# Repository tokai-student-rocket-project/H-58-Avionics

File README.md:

# H-58 搭載計器

TSRP-H-58に搭載する計器類のプログラム及び設計書を保存するレポジトリです。

## はじめに

学生ロケットの電装系を盛り上げたい思いから、全てのソースコードを含む設計を公開しています。ガバガバ開発ですので、分かりにくい点（資料がまとまっていないなど）が多々あります。ご了承ください。

ご不明な点は以下のSNSからお気軽にお問合せください。

- X (旧Twitter): [@Tokai_SRP](https://twitter.com/Tokai_SRP)

### 計器の概要

H-58搭載計器はCANBUS接続された複数のモジュールから構成されます。

### レポジトリ構成

#### ./Components/Modules/

- [SystemDataCommunicationModule](./Components/Modules/SystemDataCommunicationModule/README.md)  
- [AirDataCommunicationModule](./Components/Modules/AirDataCommunicationModule/README.md) 
- [FlightModule](./Components/Modules/FlightModule/README.md)  
- [SensingModule](./Components/Modules/SensingModule/README.md) 
- [ValveControlModule](./Components/Modules/ValveContolModule/README.md) 
- [MissionModule](./Components/Modules/MissionModule/README.md) 
- [PowerModule](./Components/Modules/PowerModule/README.md) 

#### ./Documents/

- 開発資料
  - [工程計画書](./Documents/Materials/Schedule.md)
  - [要件定義書](./Documents/Materials/RequirementsDocument.md)
  - [基本設計書](./Documents/Materials/BasicDesignDocument.md)
  - [詳細設計書](./Documents/Materials/DetailedDesignDocument.md)
- 安全審査
  - [一次審査(Z-storage)](https://docs.google.com/document/d/1F-2k9H3952sz7PHYDDPXtUgwHEACfZ0U/edit?usp=sharing&ouid=102715455383884127068&rtpof=true&sd=true)
  - [二次審査(Z-storage)](https://drive.google.com/file/d/1VNDg2A9r9_NxHciDonn3Oh5dWTKx7AV1/view?usp=sharing)
- マニュアル
  - [部品一覧](./Documents/Materials/Manual/PartsList.md)
  - 手順書
    - [組み立て手順書](./Documents/Materials/Manual/Procedure/AssemblyProcedure.md)
- [詳細報告書](./Documents/Reports/DetailedRaport.pdf) (一番情報量多い)

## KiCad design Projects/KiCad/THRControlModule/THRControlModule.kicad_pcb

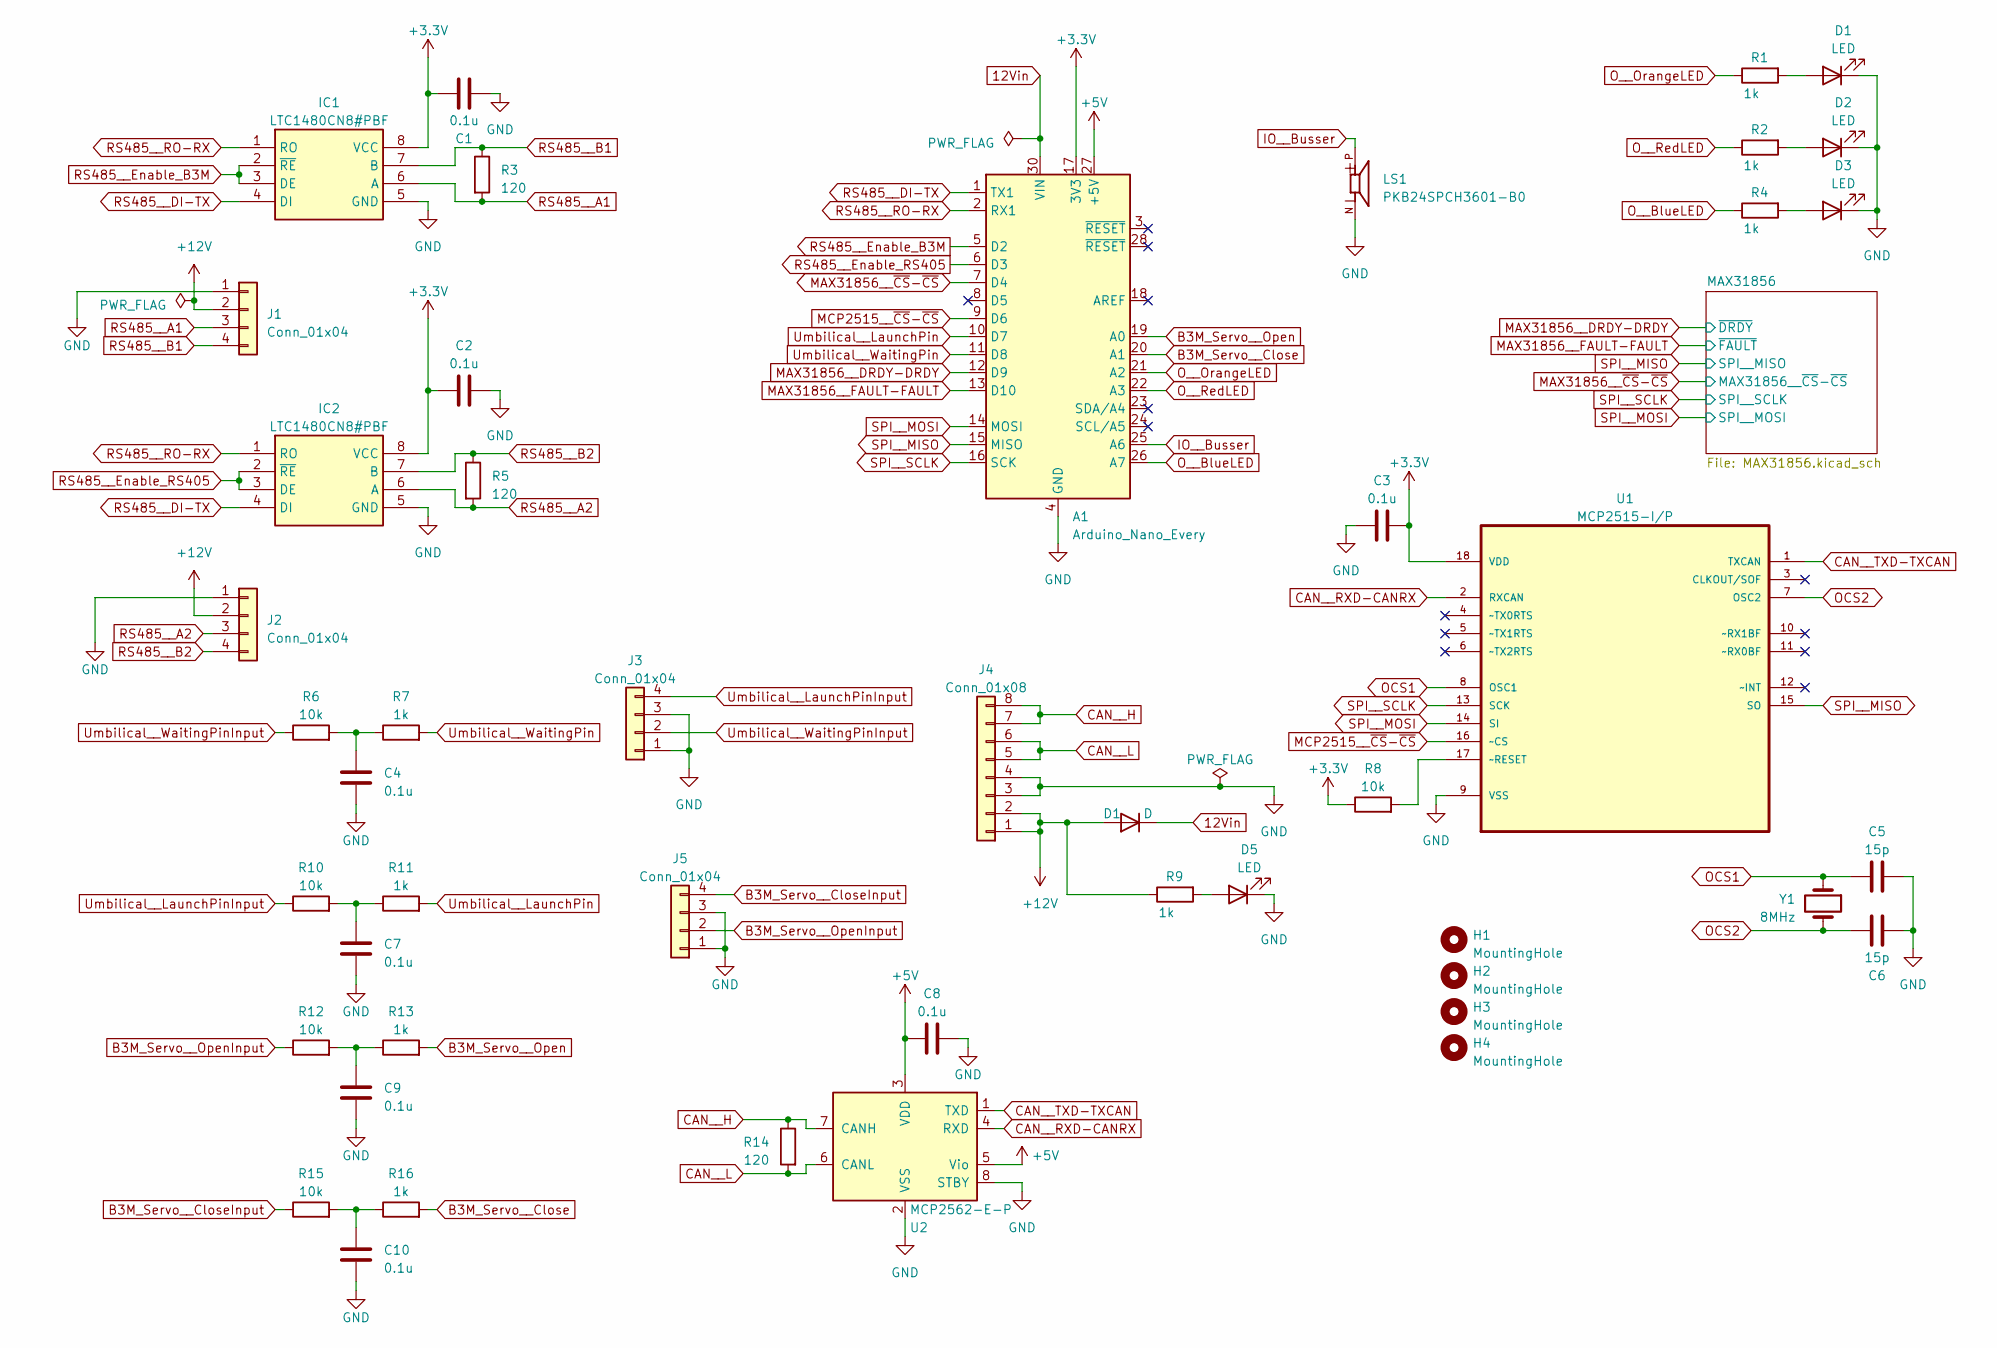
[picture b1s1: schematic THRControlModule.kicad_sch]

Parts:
A1: Arduino_Nano_Every; Arduino_Nano
C1, C2, C3, C4, C7, C8, C9, C10: 0.1u; C_0603_1608Metric_Pad1.08x0.95mm_HandSolder
C5, C6: 15p; C_0603_1608Metric_Pad1.08x0.95mm_HandSolder
D1: D; D_SOD-123
D2, D3, D5: LED; LED_0603_1608Metric_Pad1.05x0.95mm_HandSolder
H1, H2, H3, H4: MountingHole; MountingHole_4.5mm
IC1, IC2: LTC1480CN8#PBF; DIP794W53P254L1016H394Q8N; Manufacturer_Part_Number LTC1480CN8#PBF; Mouser Part Number 584-LTC1480CN8#PBF
J1, J2, J3, J5: Conn_01x04; Hirose_DF1BZ-4P-2.5DS
J4: Conn_01x08; Hirose_DF11B-8DP-2DS
LS1: PKB24SPCH3601-B0; SPKR_PKB24SPCH3601-B0; PARTREV March 24, 2017
R1, R2, R4, R7, R9, R11, R13, R16: 1k; R_0603_1608Metric_Pad0.98x0.95mm_HandSolder
R3, R5, R14: 120; R_0603_1608Metric_Pad0.98x0.95mm_HandSolder
R6, R8, R10, R12, R15: 10k; R_0603_1608Metric_Pad0.98x0.95mm_HandSolder
U1: MCP2515-I/P; DIP254P762X432-18; MPN MCP2515-I/P
U2: MCP2562-E-P; DIP-8_W7.62mm
Y1: 8MHz; Crystal_HC49-4H_Vertical

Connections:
+3.3V: A1.17 (3V3), C1.1, C2.1, C3.2, IC1.8 (VCC), IC2.8 (VCC), R8.1, U1.18 (VDD); also elsewhere on the board
+5V: A1.27 (+5V), C8.1, U2.3 (VDD), U2.5 (Vio)
B3M_Servo__Close: A1.20 (A1), R16.2
B3M_Servo__CloseInput: J5.4, R15.1
B3M_Servo__Open: A1.19 (A0), R13.2
B3M_Servo__OpenInput: J5.2, R12.1
CAN__H: J4.7, J4.8, R14.1, U2.7 (CANH)
CAN__L: J4.5, J4.6, R14.2, U2.6 (CANL)
CAN__RXD-CANRX: U1.2 (RXCAN), U2.4 (RXD)
CAN__TXD-TXCAN: U1.1 (TXCAN), U2.1 (TXD)
IO__Busser: A1.25 (A6), LS1.P
MAX31856__DRDY-DRDY: A1.12 (D9); also elsewhere on the board
MAX31856__FAULT-FAULT: A1.13 (D10); also elsewhere on the board
MAX31856__~CS-~CS: A1.7 (D4); also elsewhere on the board
MCP2515__~CS-~CS: A1.9 (D6), U1.16 (~CS)
unnamed: C4.1, R6.2, R7.1
unnamed: C7.1, R10.2, R11.1
unnamed: C9.1, R12.2, R13.1
unnamed: C10.1, R15.2, R16.1
unnamed: D2.2 (A), R2.2
unnamed: D3.2 (A), R4.2
unnamed: D5.2 (A), R9.2
unnamed: R8.2, U1.17 (~RESET)
OCS1: C5.1, U1.8 (OSC1), Y1.1
OCS2: C6.1, U1.7 (OSC2), Y1.2
O__BlueLED: A1.26 (A7), R4.1
O__OrangeLED: A1.21 (A2), R1.1
O__RedLED: A1.22 (A3), R2.1
RS485__A1: IC1.6 (A), J1.3, R3.2
RS485__A2: IC2.6 (A), J2.3, R5.2
RS485__B1: IC1.7 (B), J1.4, R3.1
RS485__B2: IC2.7 (B), J2.4, R5.1
RS485__DI-TX: A1.1 (TX1), IC1.4 (DI), IC2.4 (DI)
RS485__Enable_B3M: A1.5 (D2), IC1.2 (~RE), IC1.3 (DE)
RS485__Enable_RS405: A1.6 (D3), IC2.2 (~RE), IC2.3 (DE)
RS485__RO-RX: A1.2 (RX1), IC1.1 (RO), IC2.1 (RO)
SPI__MISO: A1.15 (MISO), U1.15 (SO); also elsewhere on the board
SPI__MOSI: A1.14 (MOSI), U1.14 (SI); also elsewhere on the board
SPI__SCLK: A1.16 (SCK), U1.13 (SCK); also elsewhere on the board
Umbilical__LaunchPin: A1.10 (D7), R11.2
Umbilical__LaunchPinInput: J3.4, R10.1
Umbilical__WaitingPin: A1.11 (D8), R7.2
Umbilical__WaitingPinInput: J3.2, R6.1

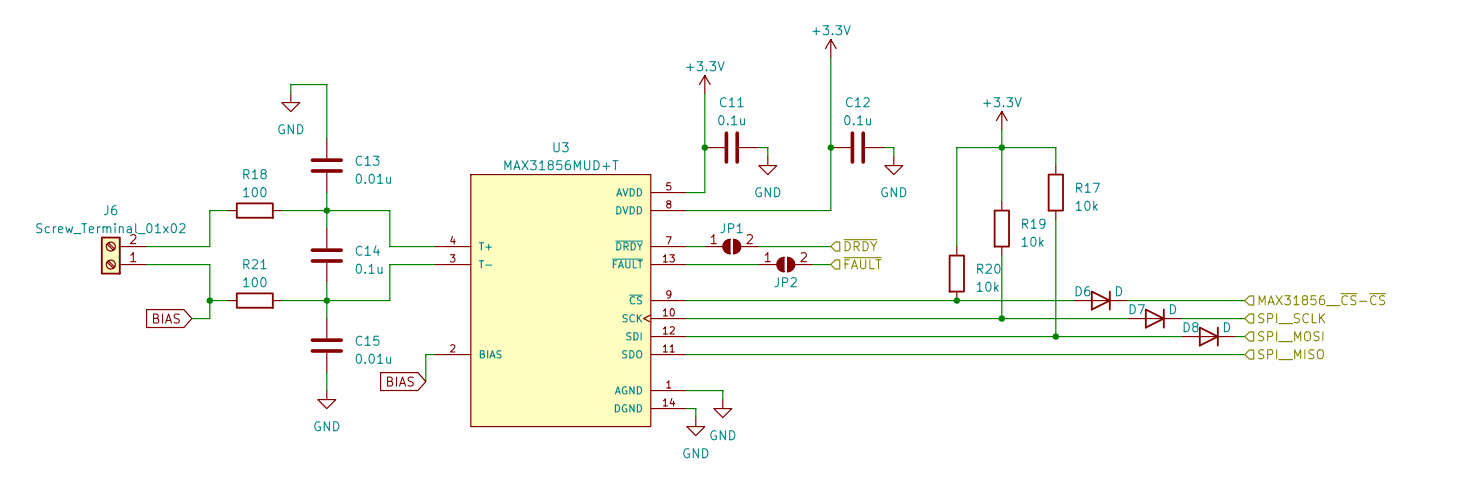
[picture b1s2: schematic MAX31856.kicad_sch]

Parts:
C11, C12, C14: 0.1u; C_0603_1608Metric_Pad1.08x0.95mm_HandSolder
C13, C15: 0.01u; C_0603_1608Metric_Pad1.08x0.95mm_HandSolder
D6, D7, D8: D; D_SOD-123
J6: Screw_Terminal_01x02; RS_PRO_611-8157
JP1, JP2: SolderJumper_2_Open; SolderJumper-2_P1.3mm_Open_Pad1.0x1.5mm
R17, R19, R20: 10k; R_0603_1608Metric_Pad0.98x0.95mm_HandSolder
R18, R21: 100; R_0805_2012Metric_Pad1.20x1.40mm_HandSolder
U3: MAX31856MUD+T; SOP65P640X110-14N; PARTREV 0

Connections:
+3.3V: C11.1, C12.1, R17.1, R19.1, R20.1, U3.5 (AVDD), U3.8 (DVDD); also elsewhere on the board
BIAS: J6.1, R21.1, U3.2 (BIAS)
MAX31856__DRDY-DRDY: JP1.2 (B); also elsewhere on the board
MAX31856__FAULT-FAULT: JP2.2 (B); also elsewhere on the board
MAX31856__~CS-~CS: D6.1 (K); also elsewhere on the board
unnamed: D6.2 (A), R20.2, U3.9 (~CS)
unnamed: D7.2 (A), R19.2, U3.10 (SCK)
unnamed: D8.2 (A), R17.2, U3.12 (SDI)
unnamed: J6.2, R18.1
unnamed: JP1.1 (A), U3.7 (~DRDY)
unnamed: JP2.1 (A), U3.13 (~FAULT)
unnamed: C13.2, C14.1, R18.2, U3.4 (T+)
unnamed: C14.2, C15.1, R21.2, U3.3 (T-)
SPI__MISO: U3.11 (SDO); also elsewhere on the board
SPI__MOSI: D8.1 (K); also elsewhere on the board
SPI__SCLK: D7.1 (K); also elsewhere on the board

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
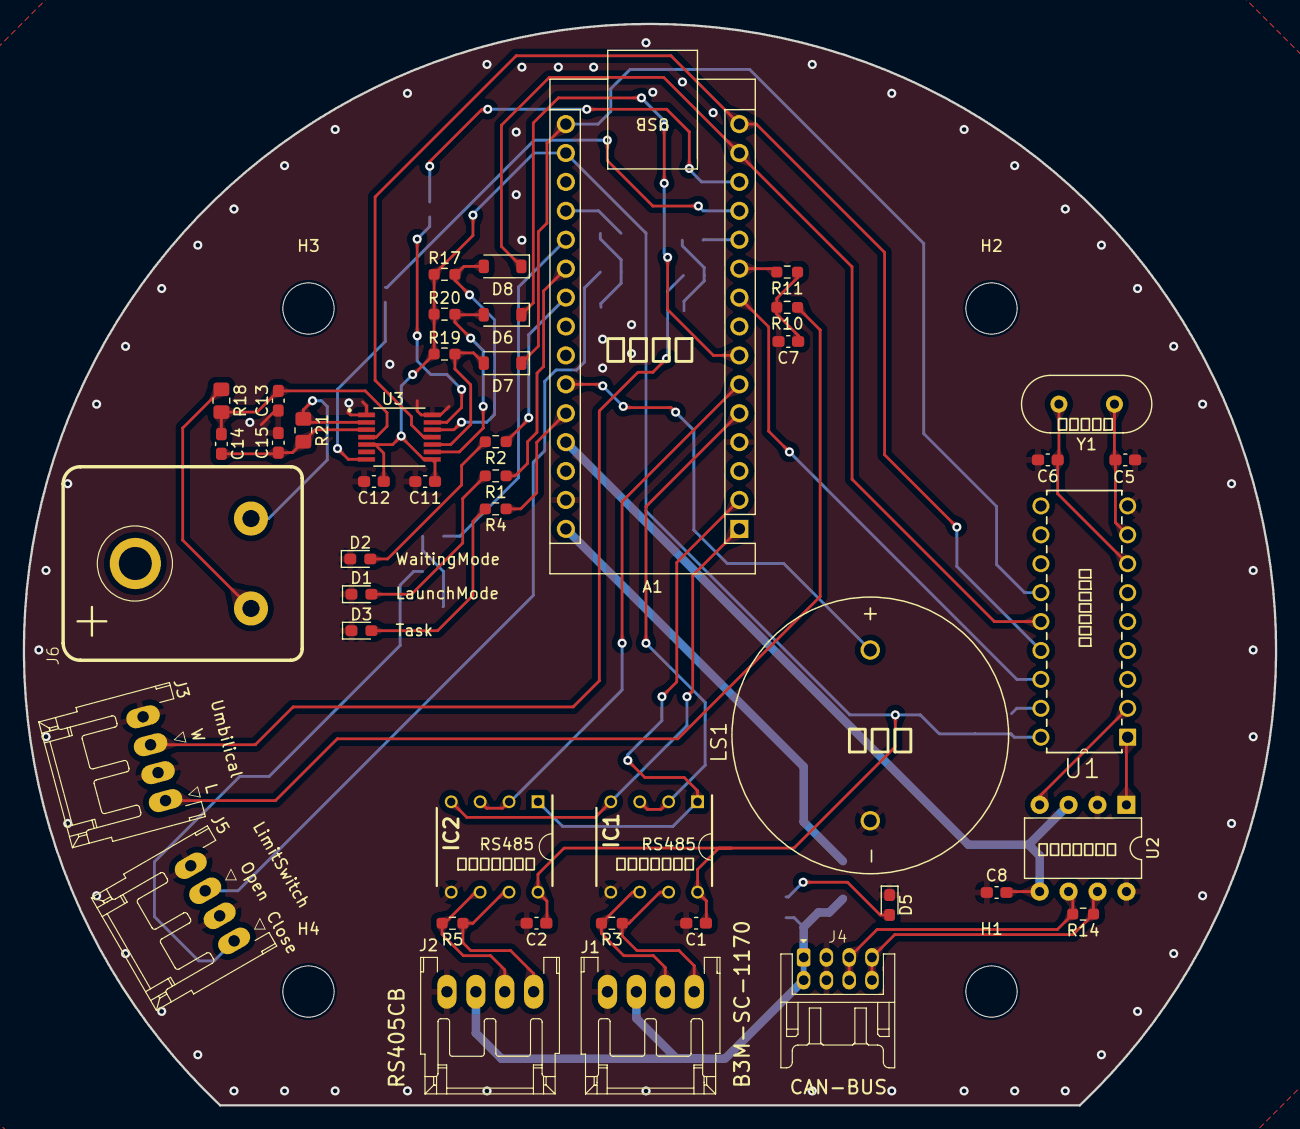
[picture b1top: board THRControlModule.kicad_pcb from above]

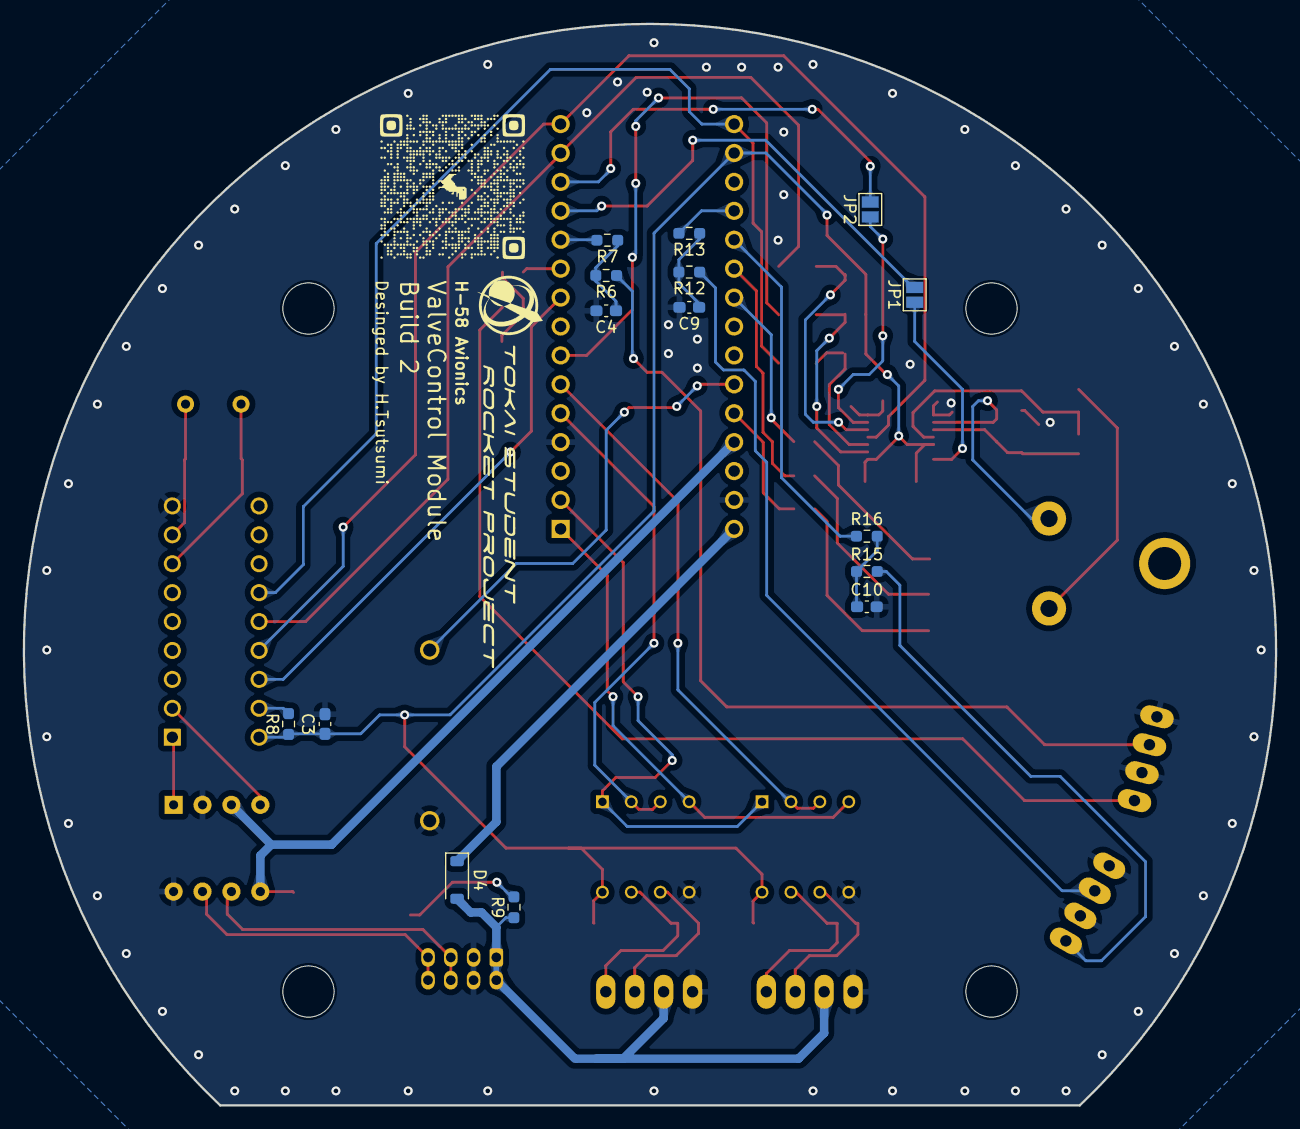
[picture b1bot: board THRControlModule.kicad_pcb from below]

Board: 2 copper layers, 110.0 x 95.0 mm, 64 parts (15 on the bottom side), 56 nets.

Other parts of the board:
D4: D; D_SOD-123

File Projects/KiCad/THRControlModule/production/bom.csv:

Designator,Footprint,Quantity,Value,LCSC Part #
A1,Arduino_Nano,1,Arduino_Nano_Every,
"C1, C10, C11, C12, C14, C2, C3, C4, C7, C8, C9",0603,11,0.1u,
"C13, C15",0603,2,0.01u,
"C5, C6",0603,2,15p,
"D1, D2, D3, D5",0603,4,LED,
"D4, D6, D7, D8",D_SOD-123,4,D,
"H1, H2, H3, H4",MountingHole_4.5mm,4,MountingHole,
"IC1, IC2",DIP794W53P254L1016H394Q8N,2,LTC1480CN8#PBF,
"J1, J2, J3, J5",Hirose_DF1BZ-4P-2.5DS,4,Conn_01x04,
J4,Hirose_DF11B-8DP-2DS,1,Conn_01x08,
J6,RS_PRO_611-8157,1,Screw_Terminal_01x02,
"JP1, JP2",SolderJumper-2_P1.3mm_Open_Pad1.0x1.5mm,2,SolderJumper_2_Open,
LS1,SPKR_PKB24SPCH3601-B0,1,PKB24SPCH3601-B0,
"R1, R11, R13, R16, R2, R4, R7, R9",0603,8,1k,
"R10, R12, R15, R17, R19, R20, R6, R8",0603,8,10k,
"R14, R3, R5",0603,3,120,
"R18, R21",0805,2,100,
U1,DIP254P762X432-18,1,MCP2515-I/P,MCP2515-I/P
U2,DIP-8_W7.62mm,1,MCP2562-E-P,
U3,SOP65P640X110-14N,1,MAX31856MUD+T,
Y1,Crystal_HC49-4H_Vertical,1,8MHz,

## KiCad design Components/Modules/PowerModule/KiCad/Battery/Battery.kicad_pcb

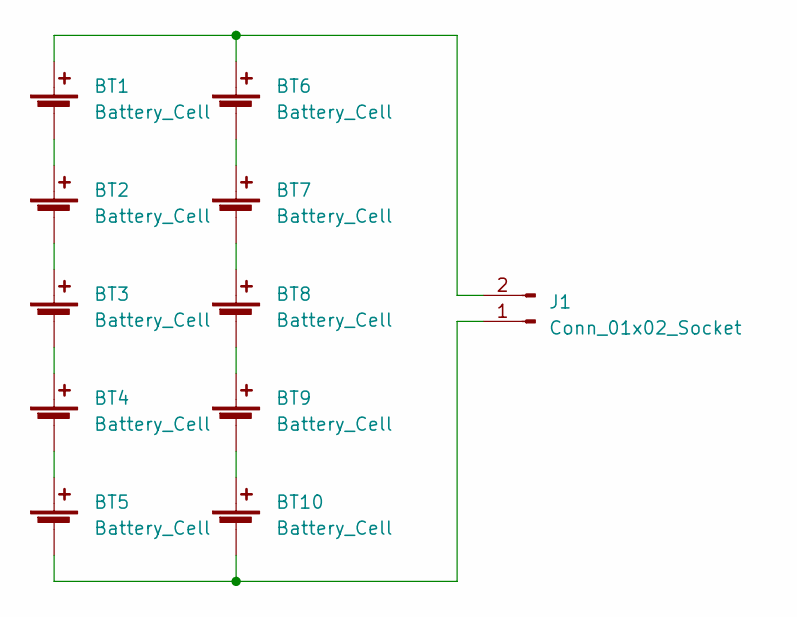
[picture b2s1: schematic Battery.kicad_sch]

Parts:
BT1, BT2, BT3, BT4, BT5, BT6, BT7, BT8, BT9, BT10: Battery_Cell; CR123APC
J1: Conn_01x02_Socket; CONNECTOR_2-STRAIGHT

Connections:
unnamed: BT1.1 (+), BT6.1 (+), J1.2
unnamed: BT1.2 (-), BT2.1 (+)
unnamed: BT2.2 (-), BT3.1 (+)
unnamed: BT3.2 (-), BT4.1 (+)
unnamed: BT4.2 (-), BT5.1 (+)
unnamed: BT6.2 (-), BT7.1 (+)
unnamed: BT7.2 (-), BT8.1 (+)
unnamed: BT8.2 (-), BT9.1 (+)
unnamed: BT9.2 (-), BT10.1 (+)
unnamed: BT5.2 (-), BT10.2 (-), J1.1

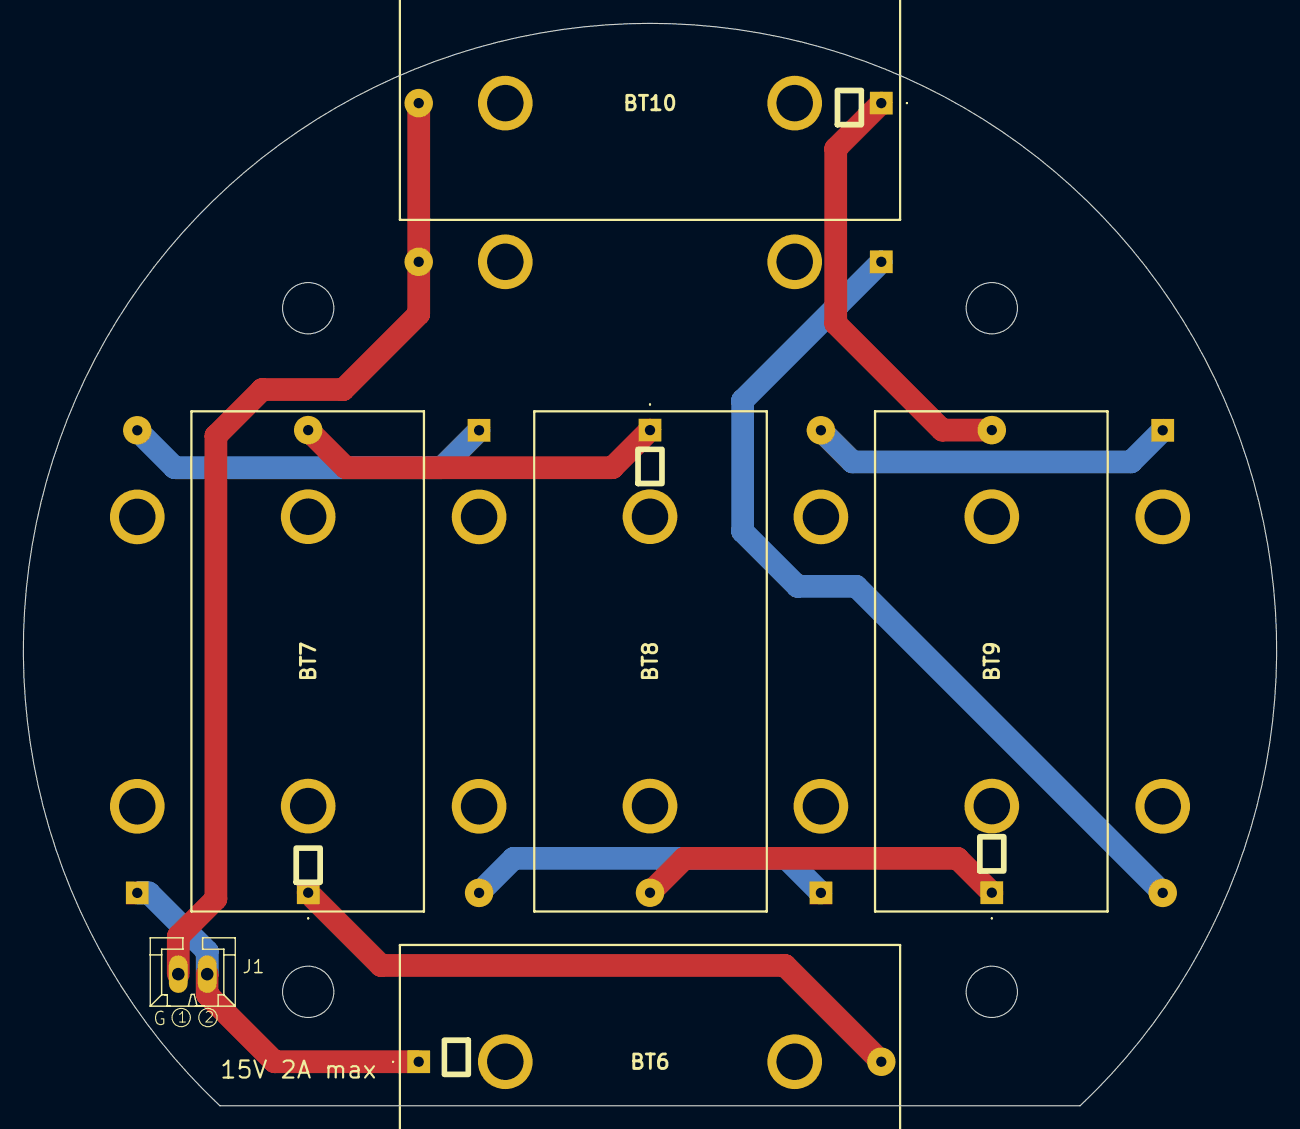
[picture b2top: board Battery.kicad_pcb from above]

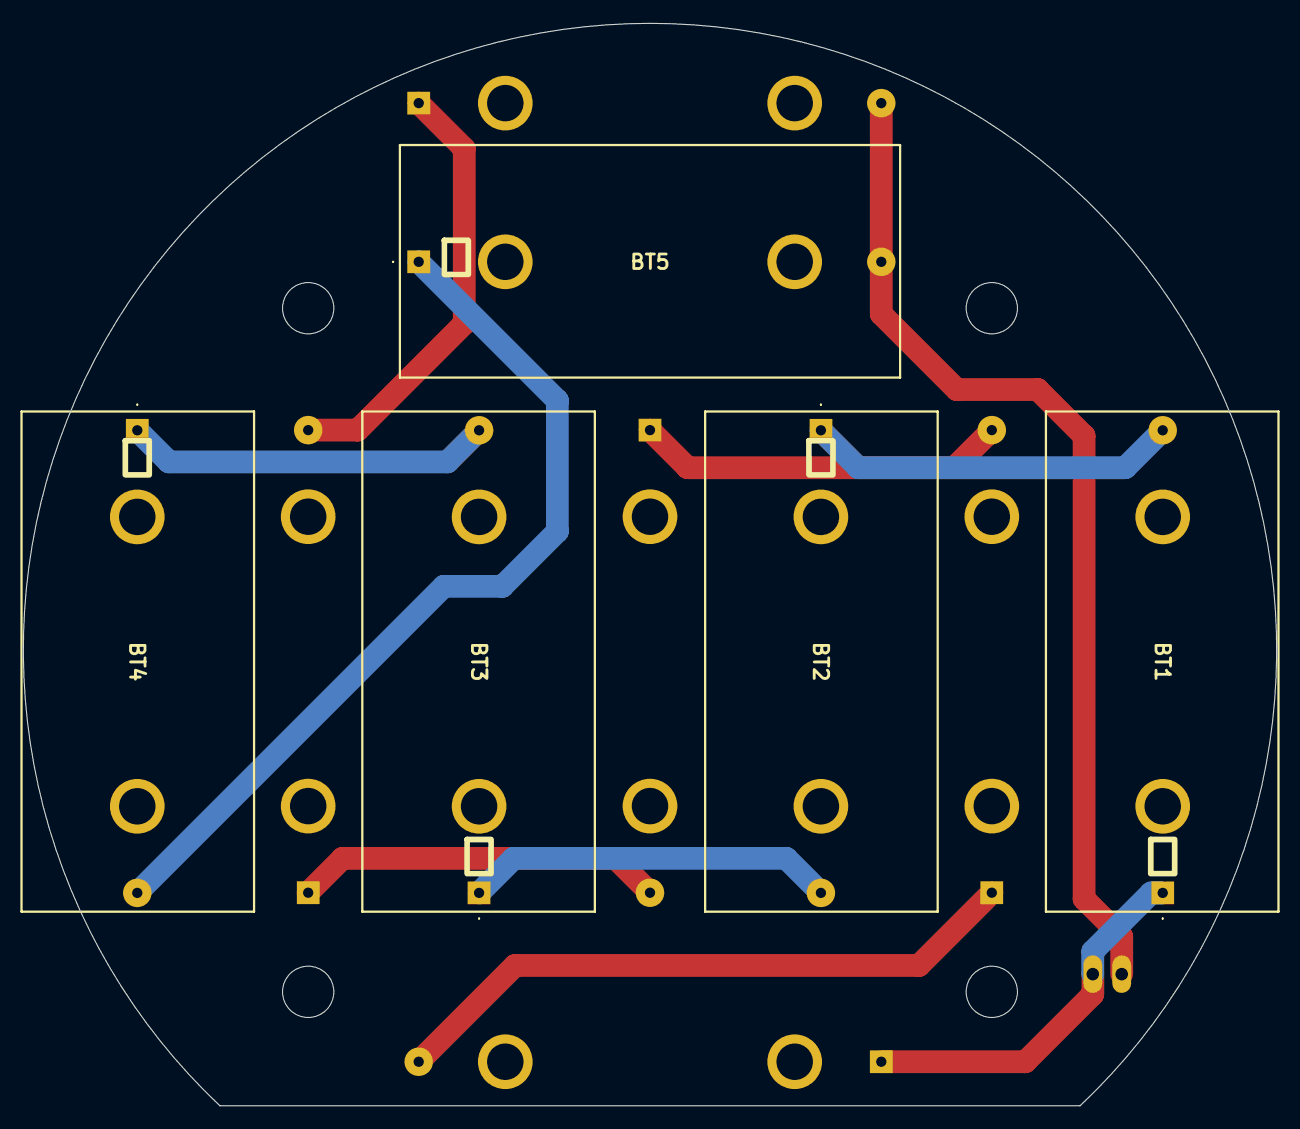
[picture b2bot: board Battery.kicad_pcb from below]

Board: 2 copper layers, 110.0 x 95.0 mm, 11 parts (5 on the bottom side), 10 nets.

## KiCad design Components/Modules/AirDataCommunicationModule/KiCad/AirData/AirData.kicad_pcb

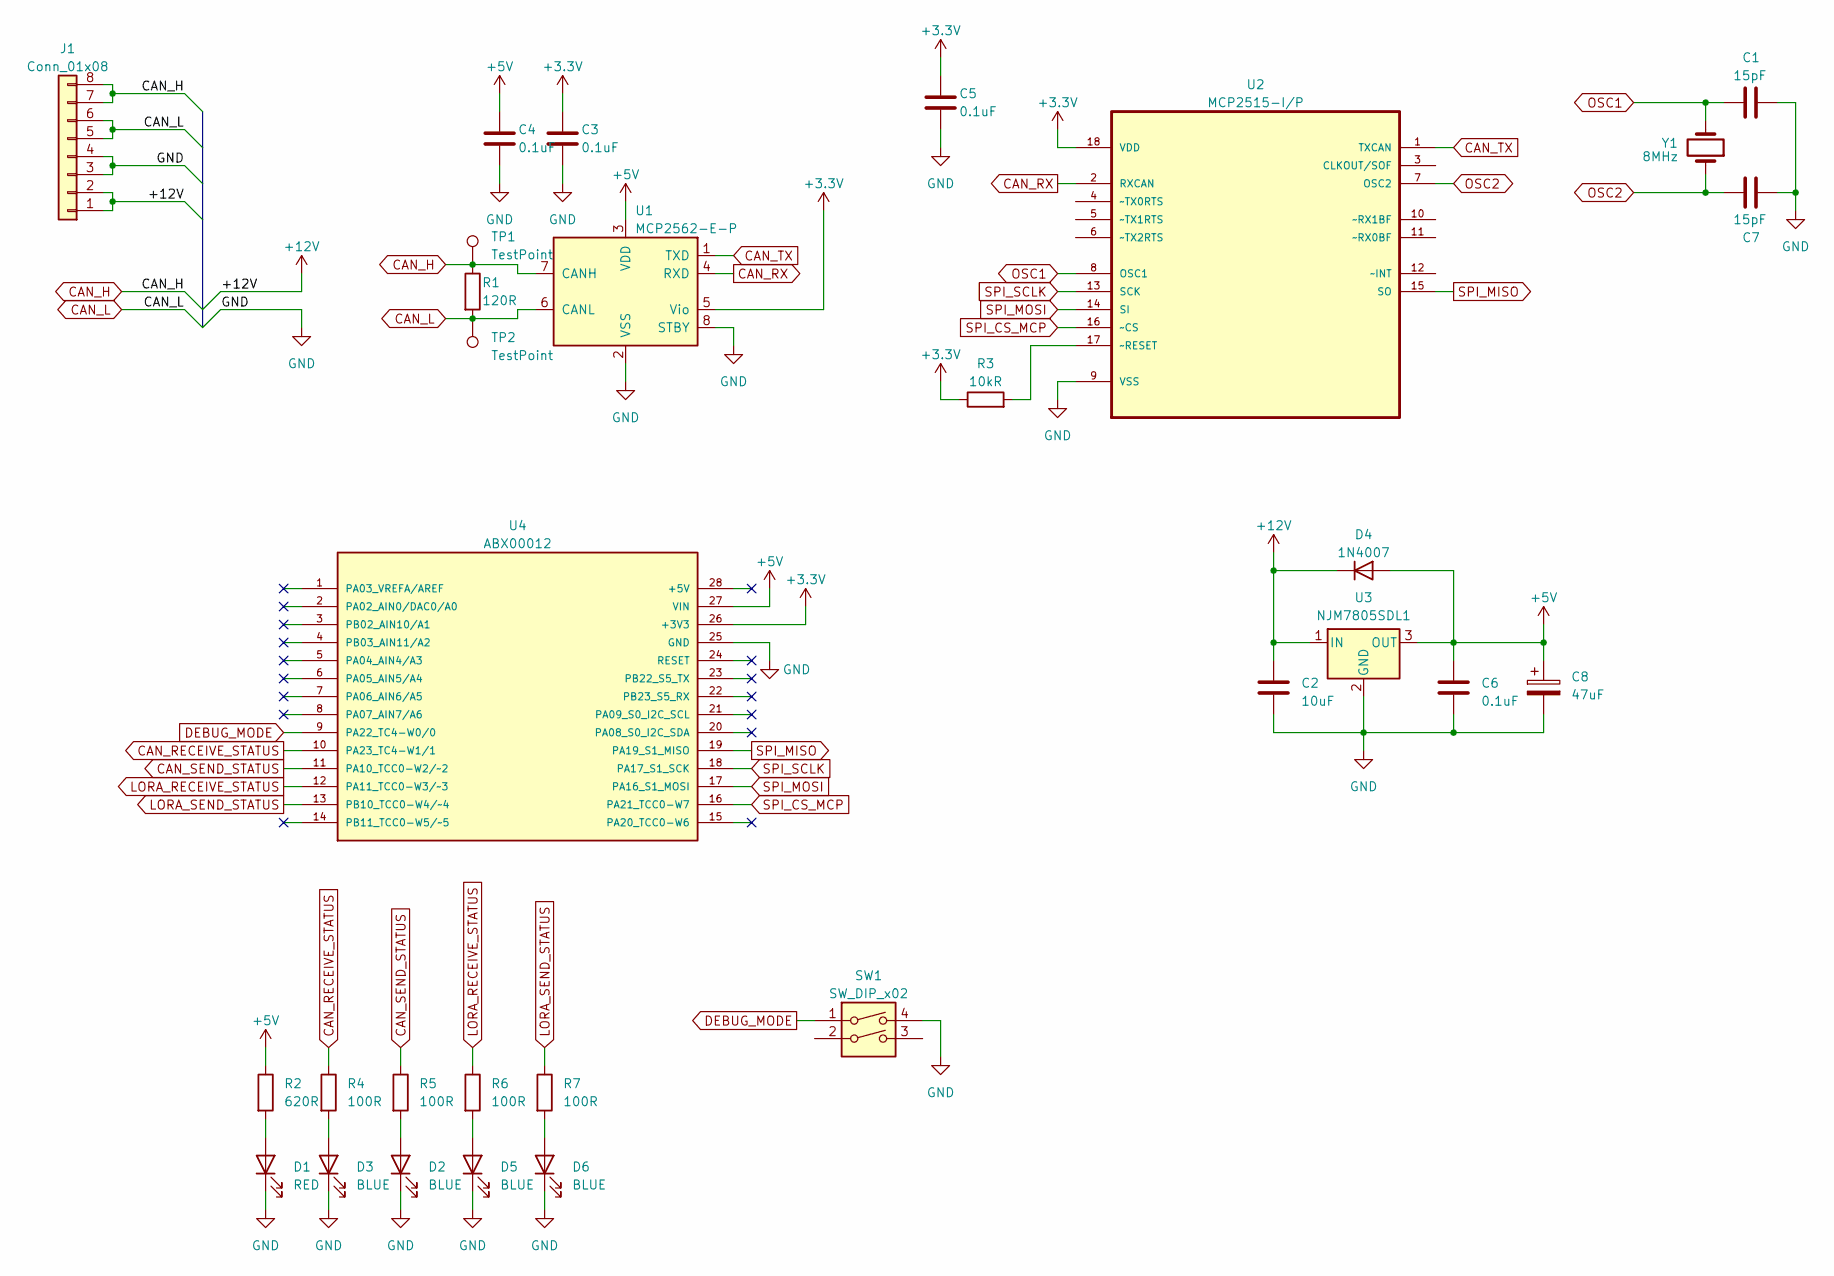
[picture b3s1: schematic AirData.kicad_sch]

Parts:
C1, C7: 15pF; C_0603_1608Metric_Pad1.08x0.95mm_HandSolder
C2: 10uF; C_0603_1608Metric_Pad1.08x0.95mm_HandSolder
C3, C4, C5, C6: 0.1uF; C_0603_1608Metric_Pad1.08x0.95mm_HandSolder
C8: 47uF; CP_Elec_6.3x5.9
D1: RED; LED_0603_1608Metric_Pad1.05x0.95mm_HandSolder
D2, D3, D5, D6: BLUE; LED_0603_1608Metric_Pad1.05x0.95mm_HandSolder
D4: 1N4007; D_SOD-123F
J1: Conn_01x08; Hirose_DF11B-8DP-2DS
R1: 120R; R_0603_1608Metric_Pad0.98x0.95mm_HandSolder
R2: 620R; R_0603_1608Metric_Pad0.98x0.95mm_HandSolder
R3: 10kR; R_0805_2012Metric_Pad1.20x1.40mm_HandSolder
R4, R5, R6, R7: 100R; R_0805_2012Metric_Pad1.20x1.40mm_HandSolder
SW1: SW_DIP_x02; SW_DIP_SPSTx02_Piano_10.8x6.64mm_W7.62mm_P2.54mm
TP1, TP2: TestPoint; Pin_D1.0mm_L10.0mm
U1: MCP2562-E-P; DIP-8_W7.62mm
U2: MCP2515-I/P; DIP-18_W7.62mm; MPN MCP2515-I/P
U3: NJM7805SDL1; TO-252-2
U4: ABX00012; ARDUINO_ABX00012; PARTREV 5
Y1: 8MHz; Crystal_SMD_HC49-SD

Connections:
+3.3V: C3.1, C5.1, R3.1, U1.5 (Vio), U2.18 (VDD), U4.26 (+3V3)
+5V: C4.1, C6.1, C8.1, D4.2 (A), R2.1, U1.3 (VDD), U3.3 (OUT), U4.27 (VIN)
+12V: C2.1, D4.1 (K), J1.1, J1.2, U3.1 (IN)
CAN_H: J1.7, J1.8, R1.1, TP1.1, U1.7 (CANH)
CAN_L: J1.5, J1.6, R1.2, TP2.1, U1.6 (CANL)
CAN_RECEIVE_STATUS: R4.1, U4.10 (PA23_TC4-W1/1)
CAN_RX: U1.4 (RXD), U2.2 (RXCAN)
CAN_SEND_STATUS: R5.1, U4.11 (PA10_TCC0-W2/~2)
CAN_TX: U1.1 (TXD), U2.1 (TXCAN)
DEBUG_MODE: SW1.1, U4.9 (PA22_TC4-W0/0)
GND: C1.1, C2.2, C3.2, C4.2, C5.2, C6.2, C7.1, C8.2, D1.1 (K), D2.1 (K), D3.1 (K), D5.1 (K), D6.1 (K), J1.3, J1.4, SW1.4, U1.2 (VSS), U1.8 (STBY), U2.9 (VSS), U3.2 (GND), U4.25 (GND)
LORA_RECEIVE_STATUS: R6.1, U4.12 (PA11_TCC0-W3/~3)
LORA_SEND_STATUS: R7.1, U4.13 (PB10_TCC0-W4/~4)
unnamed: D1.2 (A), R2.2
unnamed: D2.2 (A), R5.2
unnamed: D3.2 (A), R4.2
unnamed: D5.2 (A), R6.2
unnamed: D6.2 (A), R7.2
unnamed: R3.2, U2.17 (~RESET)
OSC1: C1.2, U2.8 (OSC1), Y1.2
OSC2: C7.2, U2.7 (OSC2), Y1.1
SPI_CS_MCP: U2.16 (~CS), U4.16 (PA21_TCC0-W7)
SPI_MISO: U2.15 (SO), U4.19 (PA19_S1_MISO)
SPI_MOSI: U2.14 (SI), U4.17 (PA16_S1_MOSI)
SPI_SCLK: U2.13 (SCK), U4.18 (PA17_S1_SCK)

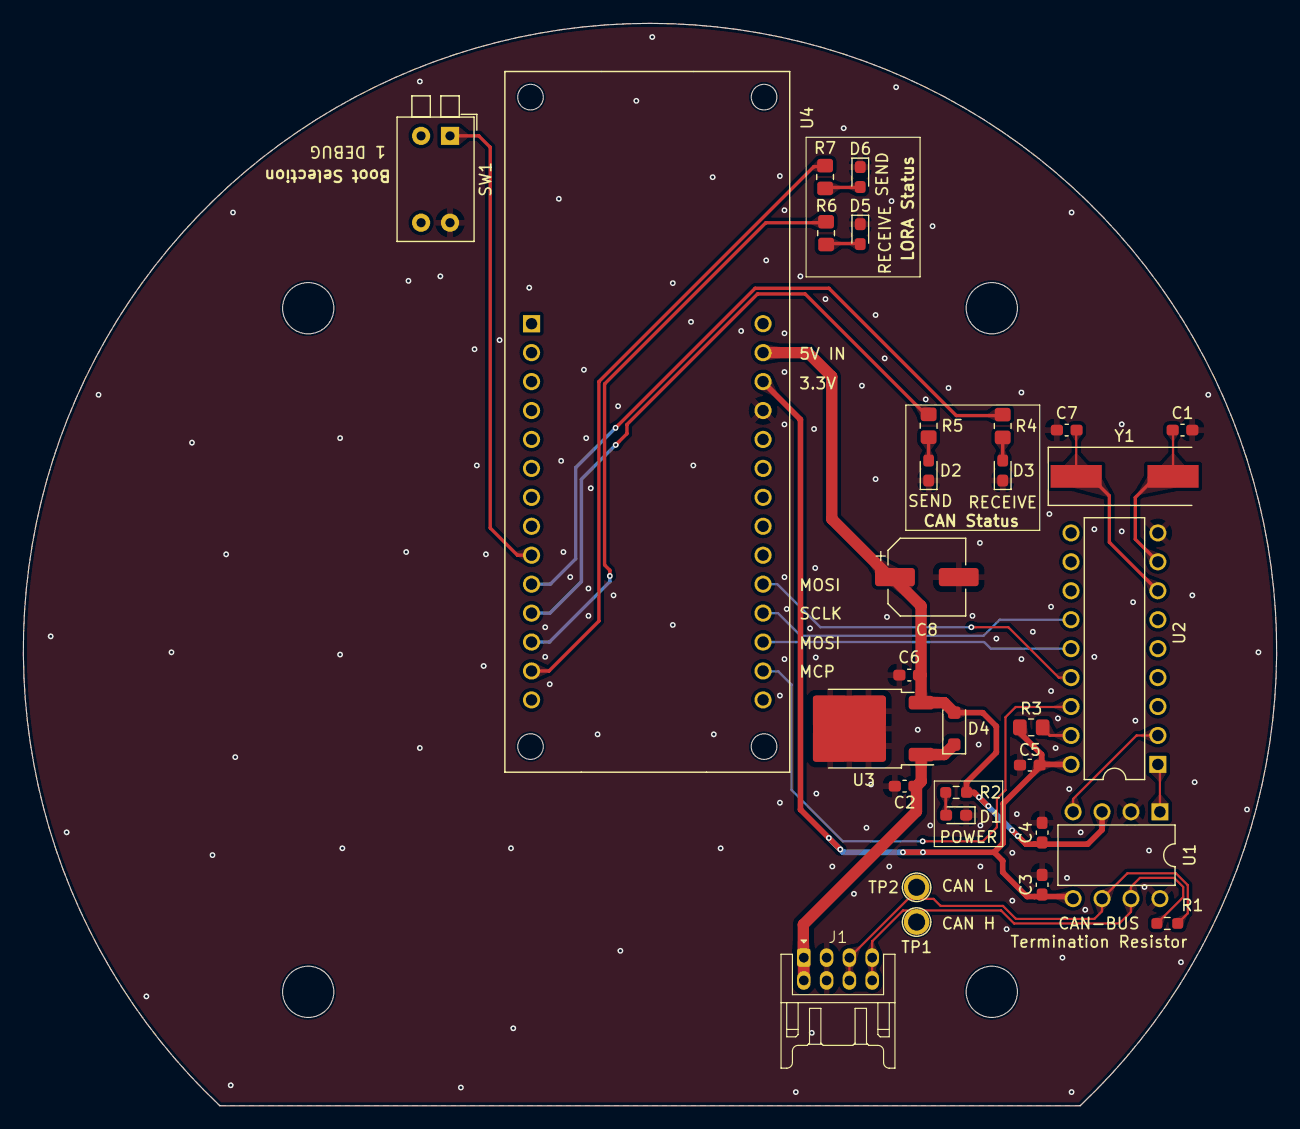
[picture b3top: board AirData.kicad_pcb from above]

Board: 2 copper layers, 110.0 x 95.0 mm, 30 parts (0 on the bottom side), 25 nets.

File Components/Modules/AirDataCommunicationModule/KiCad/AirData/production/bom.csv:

Designator,Footprint,Quantity,Value,LCSC Part #
"C1, C7",0603,2,15pF,
C2,0603,1,10uF,
"C3, C4, C5, C6",0603,4,0.1uF,
C8,CP_Elec_6.3x5.9,1,47uF,
D1,0603,1,RED,
"D2, D3, D5, D6",0603,4,BLUE,
D4,D_SOD-123F,1,1N4007,
J1,Hirose_DF11B-8DP-2DS,1,Conn_01x08,
R1,0603,1,120R,
R2,0603,1,620R,
R3,0805,1,10kR,
"R4, R5, R6, R7",0805,4,100R,
SW1,SW_DIP_SPSTx02_Piano_10.8x6.64mm_W7.62mm_P2.54mm,1,SW_DIP_x02,
"TP1, TP2",Pin_D1.0mm_L10.0mm,2,TestPoint,
U1,DIP-8_W7.62mm,1,MCP2562-E-P,
U2,DIP-18_W7.62mm,1,MCP2515-I/P,MCP2515-I/P
U3,TO-252-2,1,NJM7805SDL1,
U4,ARDUINO_ABX00012,1,ABX00012,
Y1,Crystal_SMD_HC49-SD,1,8MHz,
